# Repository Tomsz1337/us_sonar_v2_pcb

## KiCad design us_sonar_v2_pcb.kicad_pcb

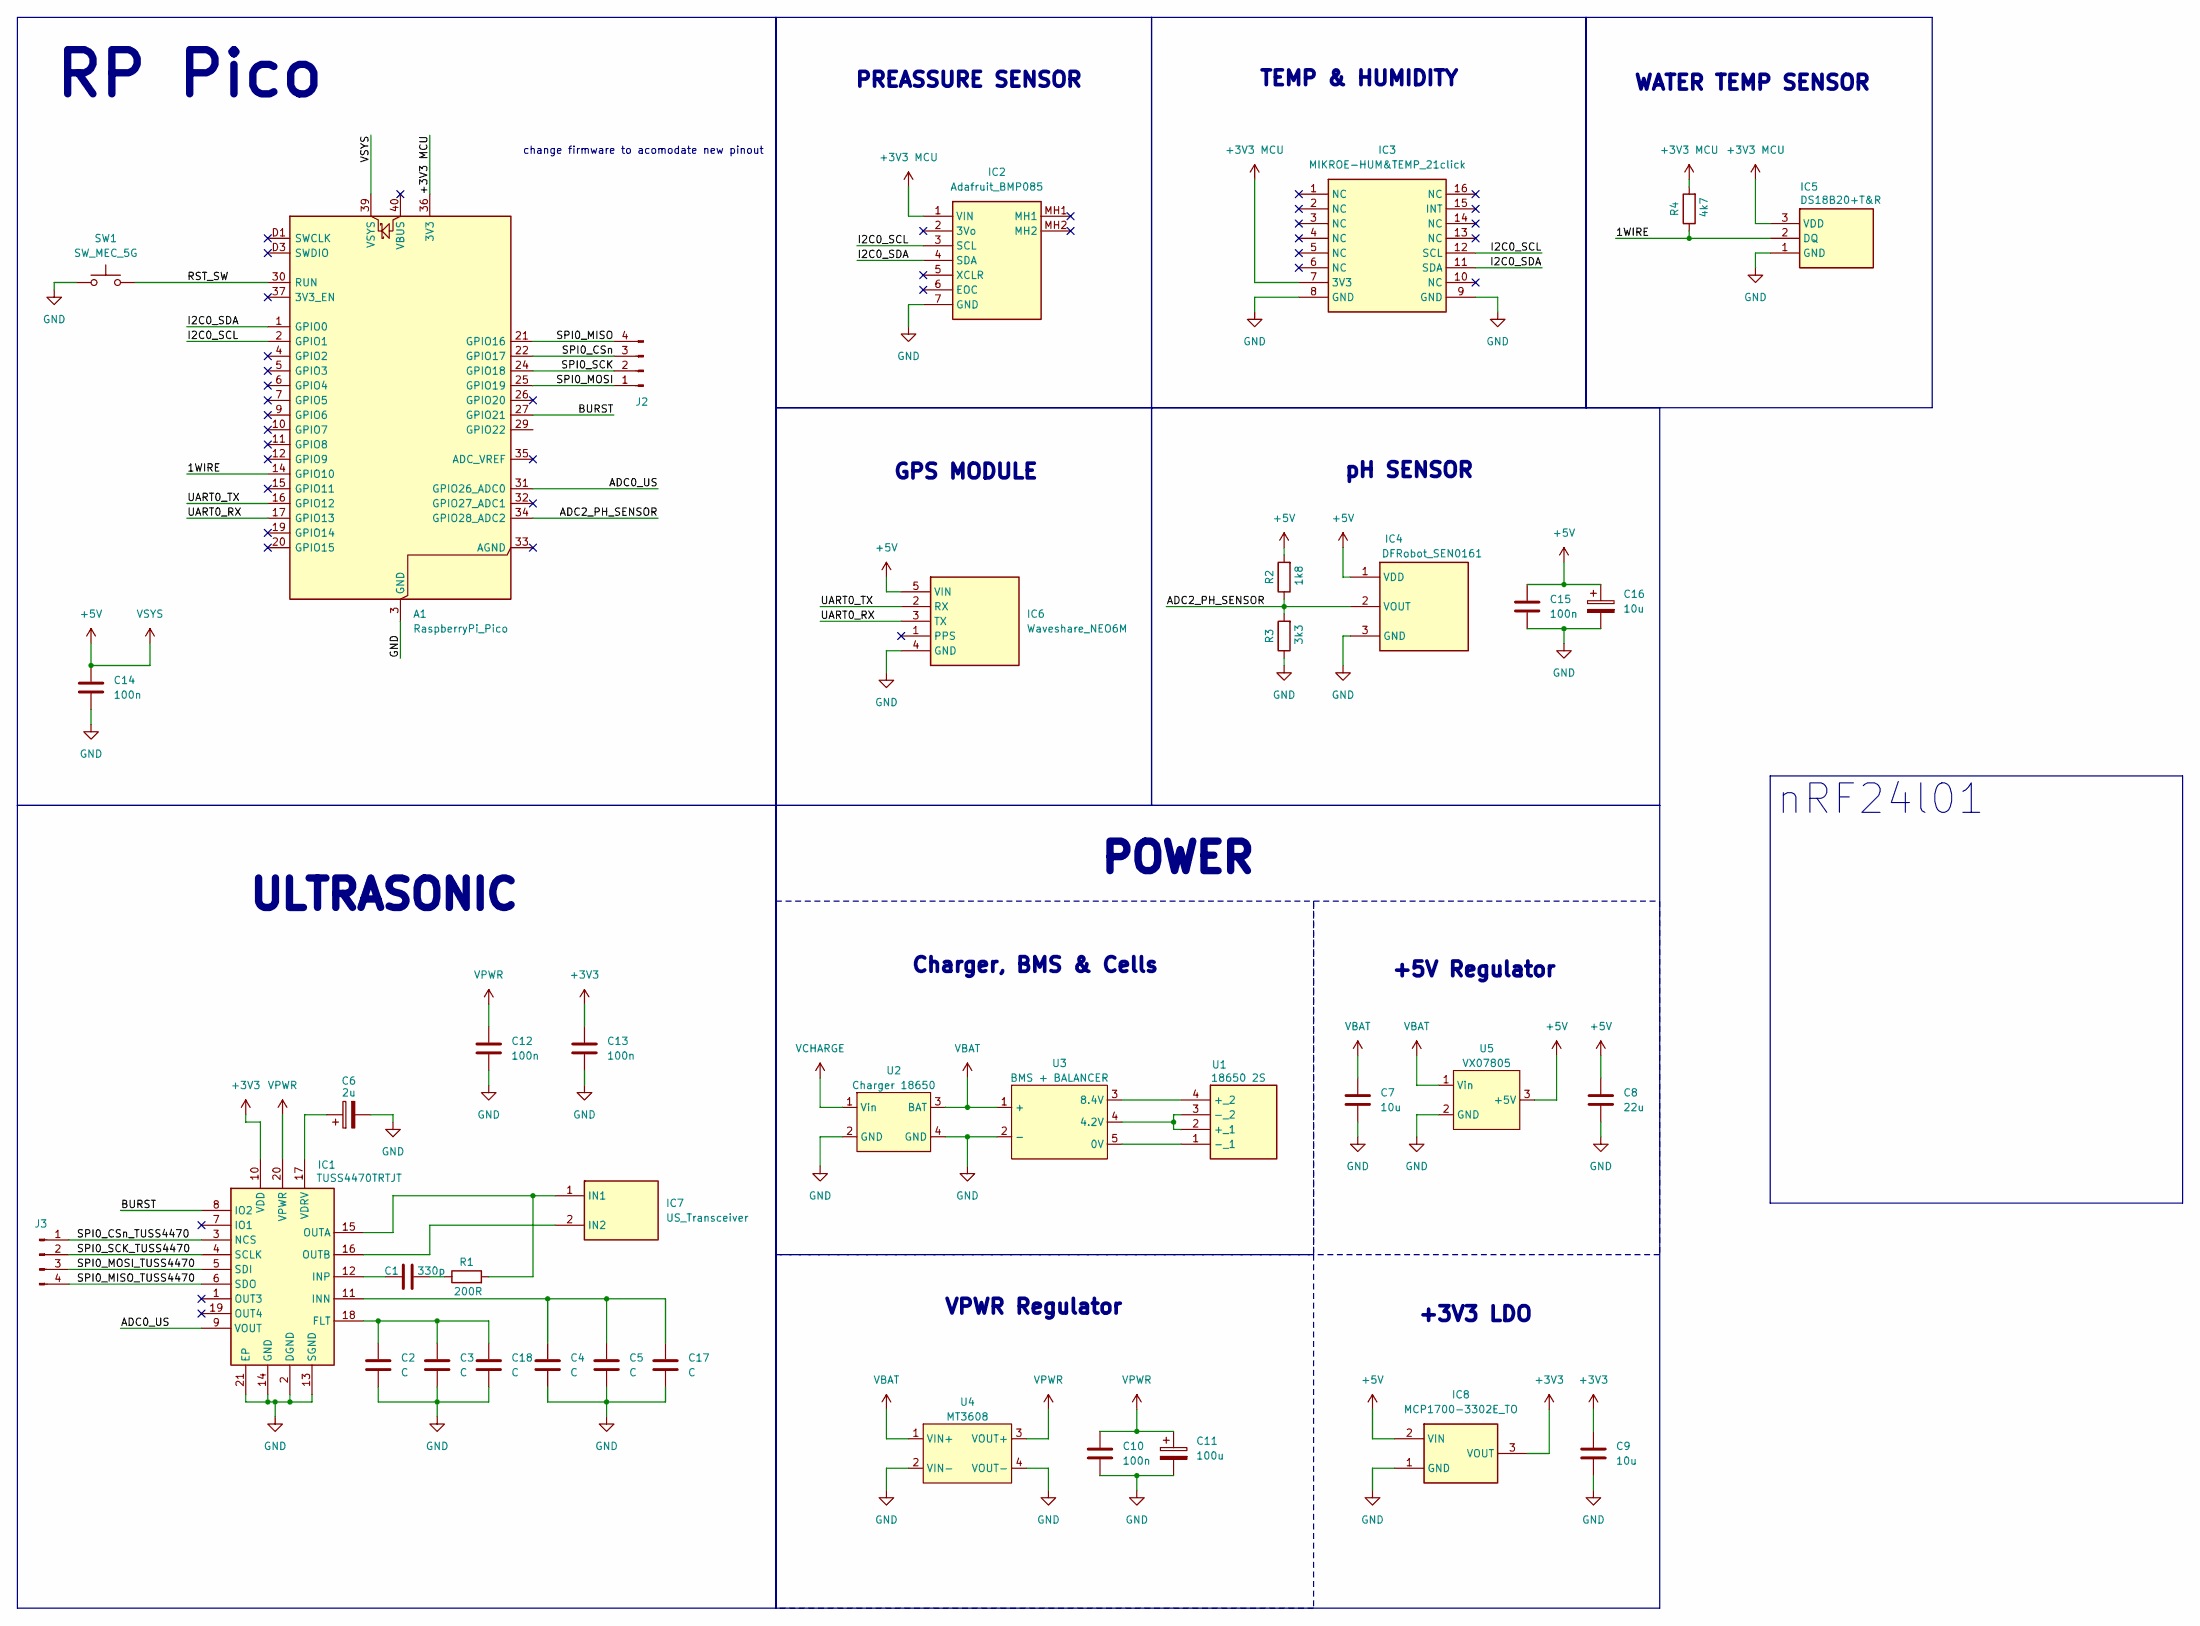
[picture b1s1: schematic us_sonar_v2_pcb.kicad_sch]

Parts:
A1: RaspberryPi_Pico; RaspberryPi_Pico_Common_THT
C1: 330p; C_0805_2012Metric_Pad1.18x1.45mm_HandSolder
C2, C3, C4, C5, C17, C18: C; C_0805_2012Metric_Pad1.18x1.45mm_HandSolder
C6: 2u; C_Radial_D8.0mm_H7.0mm_P3.50mm
C7: 10u; C_0805_2012Metric_Pad1.18x1.45mm_HandSolder
C8: 22u; C_0805_2012Metric
C9: 10u; C_0805_2012Metric
C10, C12, C13, C15: 100n; C_0805_2012Metric
C11: 100u; CP_Radial_D10.0mm_P5.00mm
C14: 100n; C_0805_2012Metric_Pad1.18x1.45mm_HandSolder
C16: 10u; CP_Radial_D5.0mm_P2.00mm
IC1: TUSS4470TRTJT; TUSS4470_DIP_ADAPTER; Mouser Part Number 595-TUSS4470TRTJT
IC2: Adafruit_BMP085; ADAFRUIT_BMP085; Mouser Part Number 485-2651
IC3: MIKROE-HUM&TEMP_21click; mikroBUS_12click_temp&hum; Mouser Part Number 932-MIKROE-1817
IC4: DFRobot_SEN0161; ph meter v1_1; Mouser Part Number 485-2651
IC5: DS18B20+T&R; water_temp; Manufacturer_Part_Number DS18B20+T&R
IC6: Waveshare_NEO6M; gps_module; Mouser Part Number 485-2651
IC7: US_Transceiver; PinSocket_1x02_P2.54mm_Vertical; Manufacturer_Part_Number DS18B20+T&R
IC8: MCP1700-3302E_TO; MCP17003302ETO; Manufacturer_Part_Number MCP1700-3302E/TO
J2, J3: Conn_01x04_Pin; PinHeader_1x04_P2.54mm_Vertical
R1: 200R; R_0805_2012Metric_Pad1.20x1.40mm_HandSolder
R2: 1k8; R_0805_2012Metric_Pad1.20x1.40mm_HandSolder
R3: 3k3; R_0805_2012Metric_Pad1.20x1.40mm_HandSolder
R4: 4k7; R_0805_2012Metric_Pad1.20x1.40mm_HandSolder
SW1: SW_MEC_5G; SW_MEC_5GSH9
U1: 18650 2S; 1048; Manufacturer_Part_Number 1048
U2: Charger 18650
U3: BMS + BALANCER; BMS 2S module
U4: MT3608; MT3608_module
U5: VX07805

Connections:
+3V3: C9.1, C13.1, IC1.10 (VDD), IC8.3 (VOUT)
+3V3 MCU: A1.36 (3V3), IC2.1 (VIN), IC3.7 (3V3), IC5.3 (VDD), R4.2
+5V: A1.39 (VSYS), C8.1, C14.1, C15.1, C16.1, IC4.1 (VDD), IC6.5 (VIN), IC8.2 (VIN), R2.2, U5.3 (+5V)
/1WIRE: A1.14 (GPIO10), IC5.2 (DQ), R4.1
/ADC0_US: A1.31 (GPIO26_ADC0), IC1.9 (VOUT)
/ADC2_PH_SENSOR: A1.34 (GPIO28_ADC2), IC4.2 (VOUT), R2.1, R3.2
/BURST: A1.27 (GPIO21), IC1.8 (IO2)
/I2C0_SCL: A1.2 (GPIO1), IC2.3 (SCL), IC3.12 (SCL)
/I2C0_SDA: A1.1 (GPIO0), IC2.4 (SDA), IC3.11 (SDA)
/RST_SW: A1.30 (RUN), SW1.3 (B), SW1.4 (B)
/SPI0_CSn: A1.22 (GPIO17), J2.3
/SPI0_CSn_TUSS4470: IC1.3 (NCS), J3.1
/SPI0_MISO: A1.21 (GPIO16), J2.4
/SPI0_MISO_TUSS4470: IC1.6 (SDO), J3.4
/SPI0_MOSI: A1.25 (GPIO19), J2.1
/SPI0_MOSI_TUSS4470: IC1.5 (SDI), J3.3
/SPI0_SCK: A1.24 (GPIO18), J2.2
/SPI0_SCK_TUSS4470: IC1.4 (SCLK), J3.2
/UART0_RX: A1.17 (GPIO13), IC6.3 (TX)
/UART0_TX: A1.16 (GPIO12), IC6.2 (RX)
GND: A1.3 (GND), A1.8 (GND), A1.13 (GND), A1.18 (GND), A1.23 (GND), A1.28 (GND), A1.38 (GND), A1.D2 (GND), C2.2, C3.2, C4.2, C5.2, C6.2, C7.2, C8.2, C9.2, C10.2, C11.2, C12.2, C13.2, C14.2, C15.2, C16.2, C17.2, C18.2, IC1.2 (DGND), IC1.13 (SGND), IC1.14 (GND), IC1.21 (EP), IC2.7 (GND), IC3.8 (GND), IC3.9 (GND), IC4.3 (GND), IC5.1 (GND), IC6.4 (GND), IC8.1 (GND), R3.1, SW1.1 (A), SW1.2 (A), U2.2 (GND), U2.4 (GND), U3.2 (-), U4.2 (VIN-), U4.4 (VOUT-), U5.2 (GND)
unnamed: C1.2, R1.1
unnamed: C2.1, C3.1, C18.1, IC1.18 (FLT)
unnamed: C4.1, C5.1, C17.1, IC1.11 (INN)
unnamed: C1.1, IC1.12 (INP)
unnamed: IC1.15 (OUTA), IC7.1 (IN1), R1.2
unnamed: IC1.16 (OUTB), IC7.2 (IN2)
unnamed: C6.1, IC1.17 (VDRV)
unnamed: U1.2 (+_1), U1.3 (-_2), U3.4 (4.2V)
unnamed: U1.4 (+_2), U3.3 (8.4V)
unnamed: U1.1 (-_1), U3.5 (0V)
VBAT: C7.1, U2.3 (BAT), U3.1 (+), U4.1 (VIN+), U5.1 (Vin)
VCHARGE: U2.1 (Vin)
VPWR: C10.1, C11.1, C12.1, IC1.20 (VPWR), U4.3 (VOUT+)

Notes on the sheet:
GPS MODULE
WATER TEMP SENSOR
Charger, BMS & Cells
+5V Regulator
VPWR Regulator
POWER
RP Pico
TEMP & HUMIDITY
+3V3 LDO
pH SENSOR
PREASSURE SENSOR
ULTRASONIC
change firmware to acomodate new pinout
nRF24l01

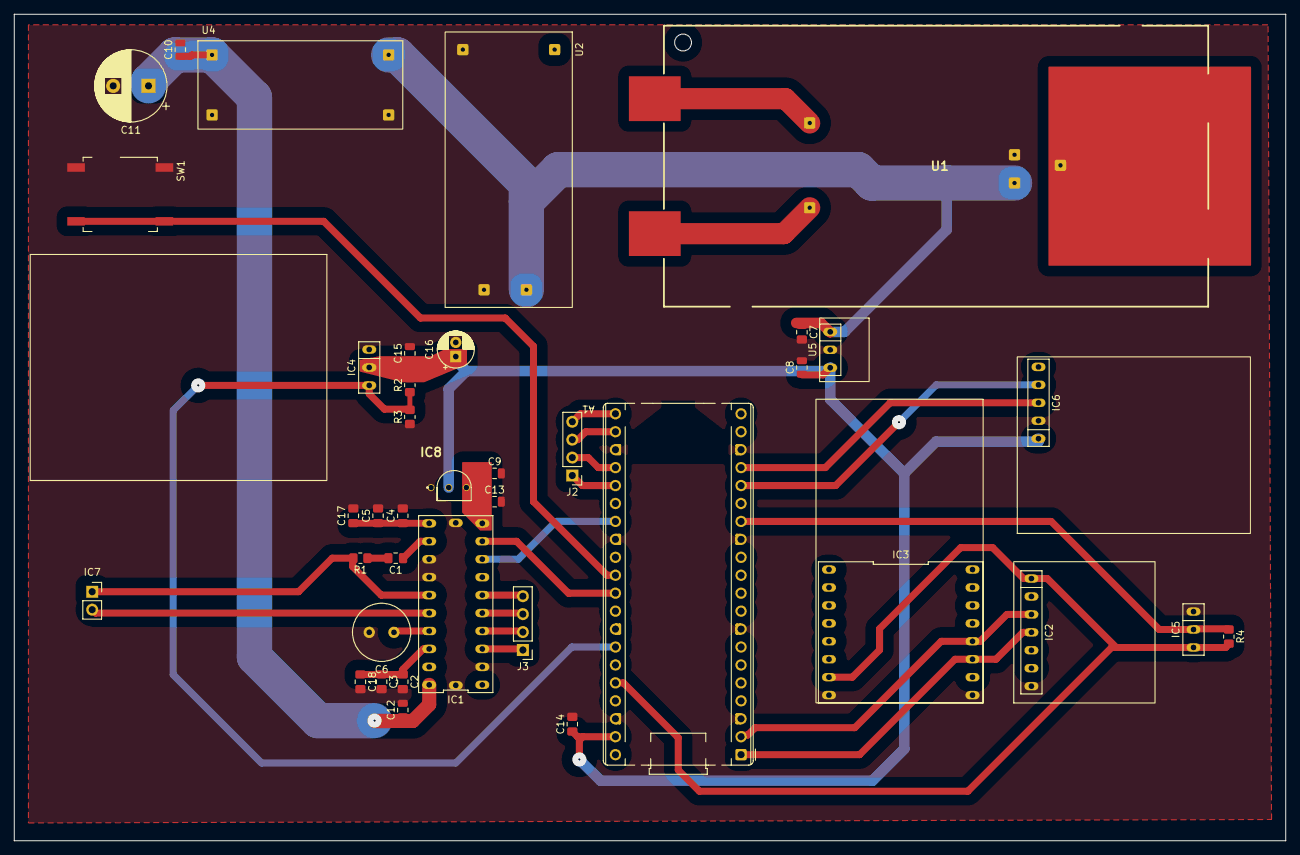
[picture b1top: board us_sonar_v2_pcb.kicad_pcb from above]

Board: 2 copper layers, 180.0 x 117.0 mm, 39 parts (1 on the bottom side), 33 nets.

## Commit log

2026-05-17 init
2026-05-20 version_1_pcb
